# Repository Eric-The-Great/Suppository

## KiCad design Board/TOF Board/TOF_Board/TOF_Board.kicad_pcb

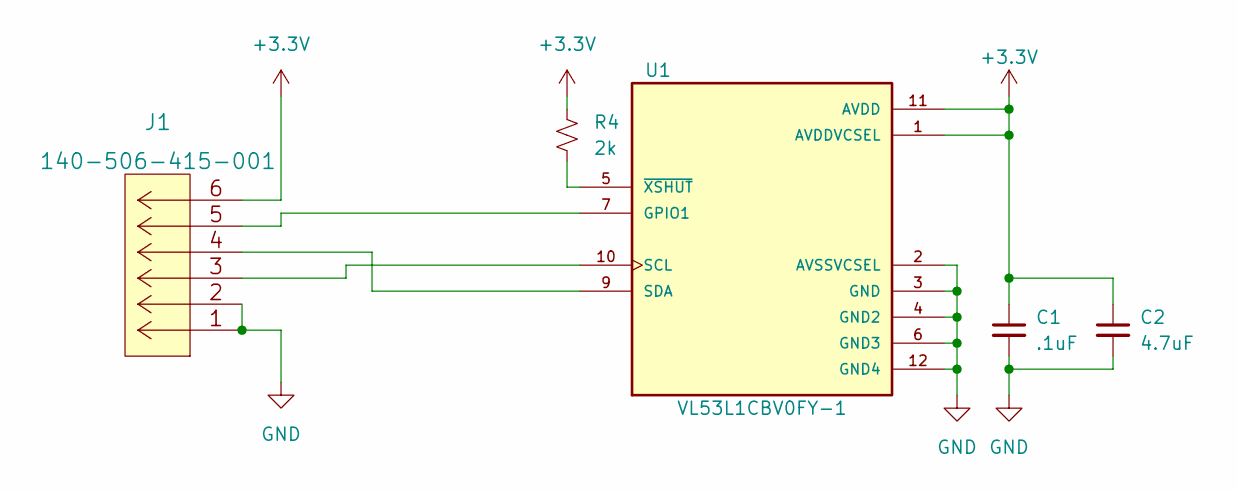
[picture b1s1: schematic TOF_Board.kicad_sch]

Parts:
C1: .1uF; R_0805_2012Metric
C2: 4.7uF; R_0805_2012Metric
J1: 140-506-415-001
R4: 2k; R_0805_2012Metric
U1: VL53L1CBV0FY-1; XDCR_VL53L1CBV0FY-1; PARTREV 3

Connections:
+3V3: C1.1, C2.1, J1.6, R4.1, U1.1 (AVDDVCSEL), U1.11 (AVDD)
GND: C1.2, C2.2, J1.1, J1.2, U1.2 (AVSSVCSEL), U1.3 (GND), U1.4 (GND2), U1.6 (GND3), U1.12 (GND4)
unnamed: J1.5, U1.7 (GPIO1)
unnamed: R4.2, U1.5 (~XSHUT)
unnamed: J1.4, U1.9 (SDA)
unnamed: J1.3, U1.10 (SCL)

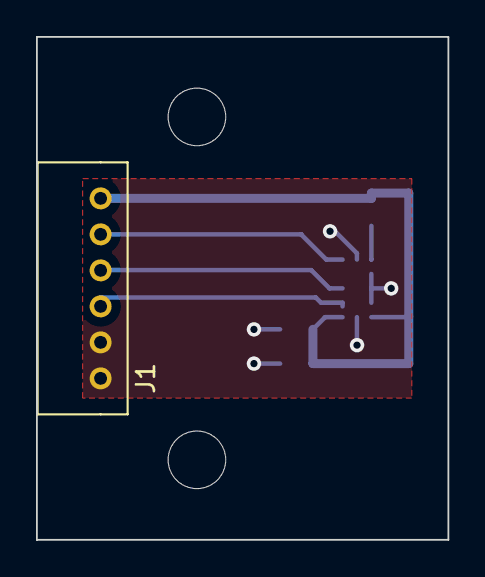
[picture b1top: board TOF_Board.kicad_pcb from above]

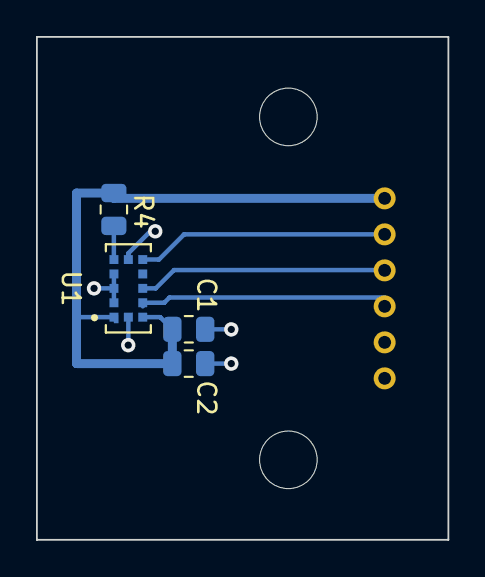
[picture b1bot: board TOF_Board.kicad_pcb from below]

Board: 2 copper layers, 22.9 x 27.9 mm, 5 parts (4 on the bottom side), 6 nets.

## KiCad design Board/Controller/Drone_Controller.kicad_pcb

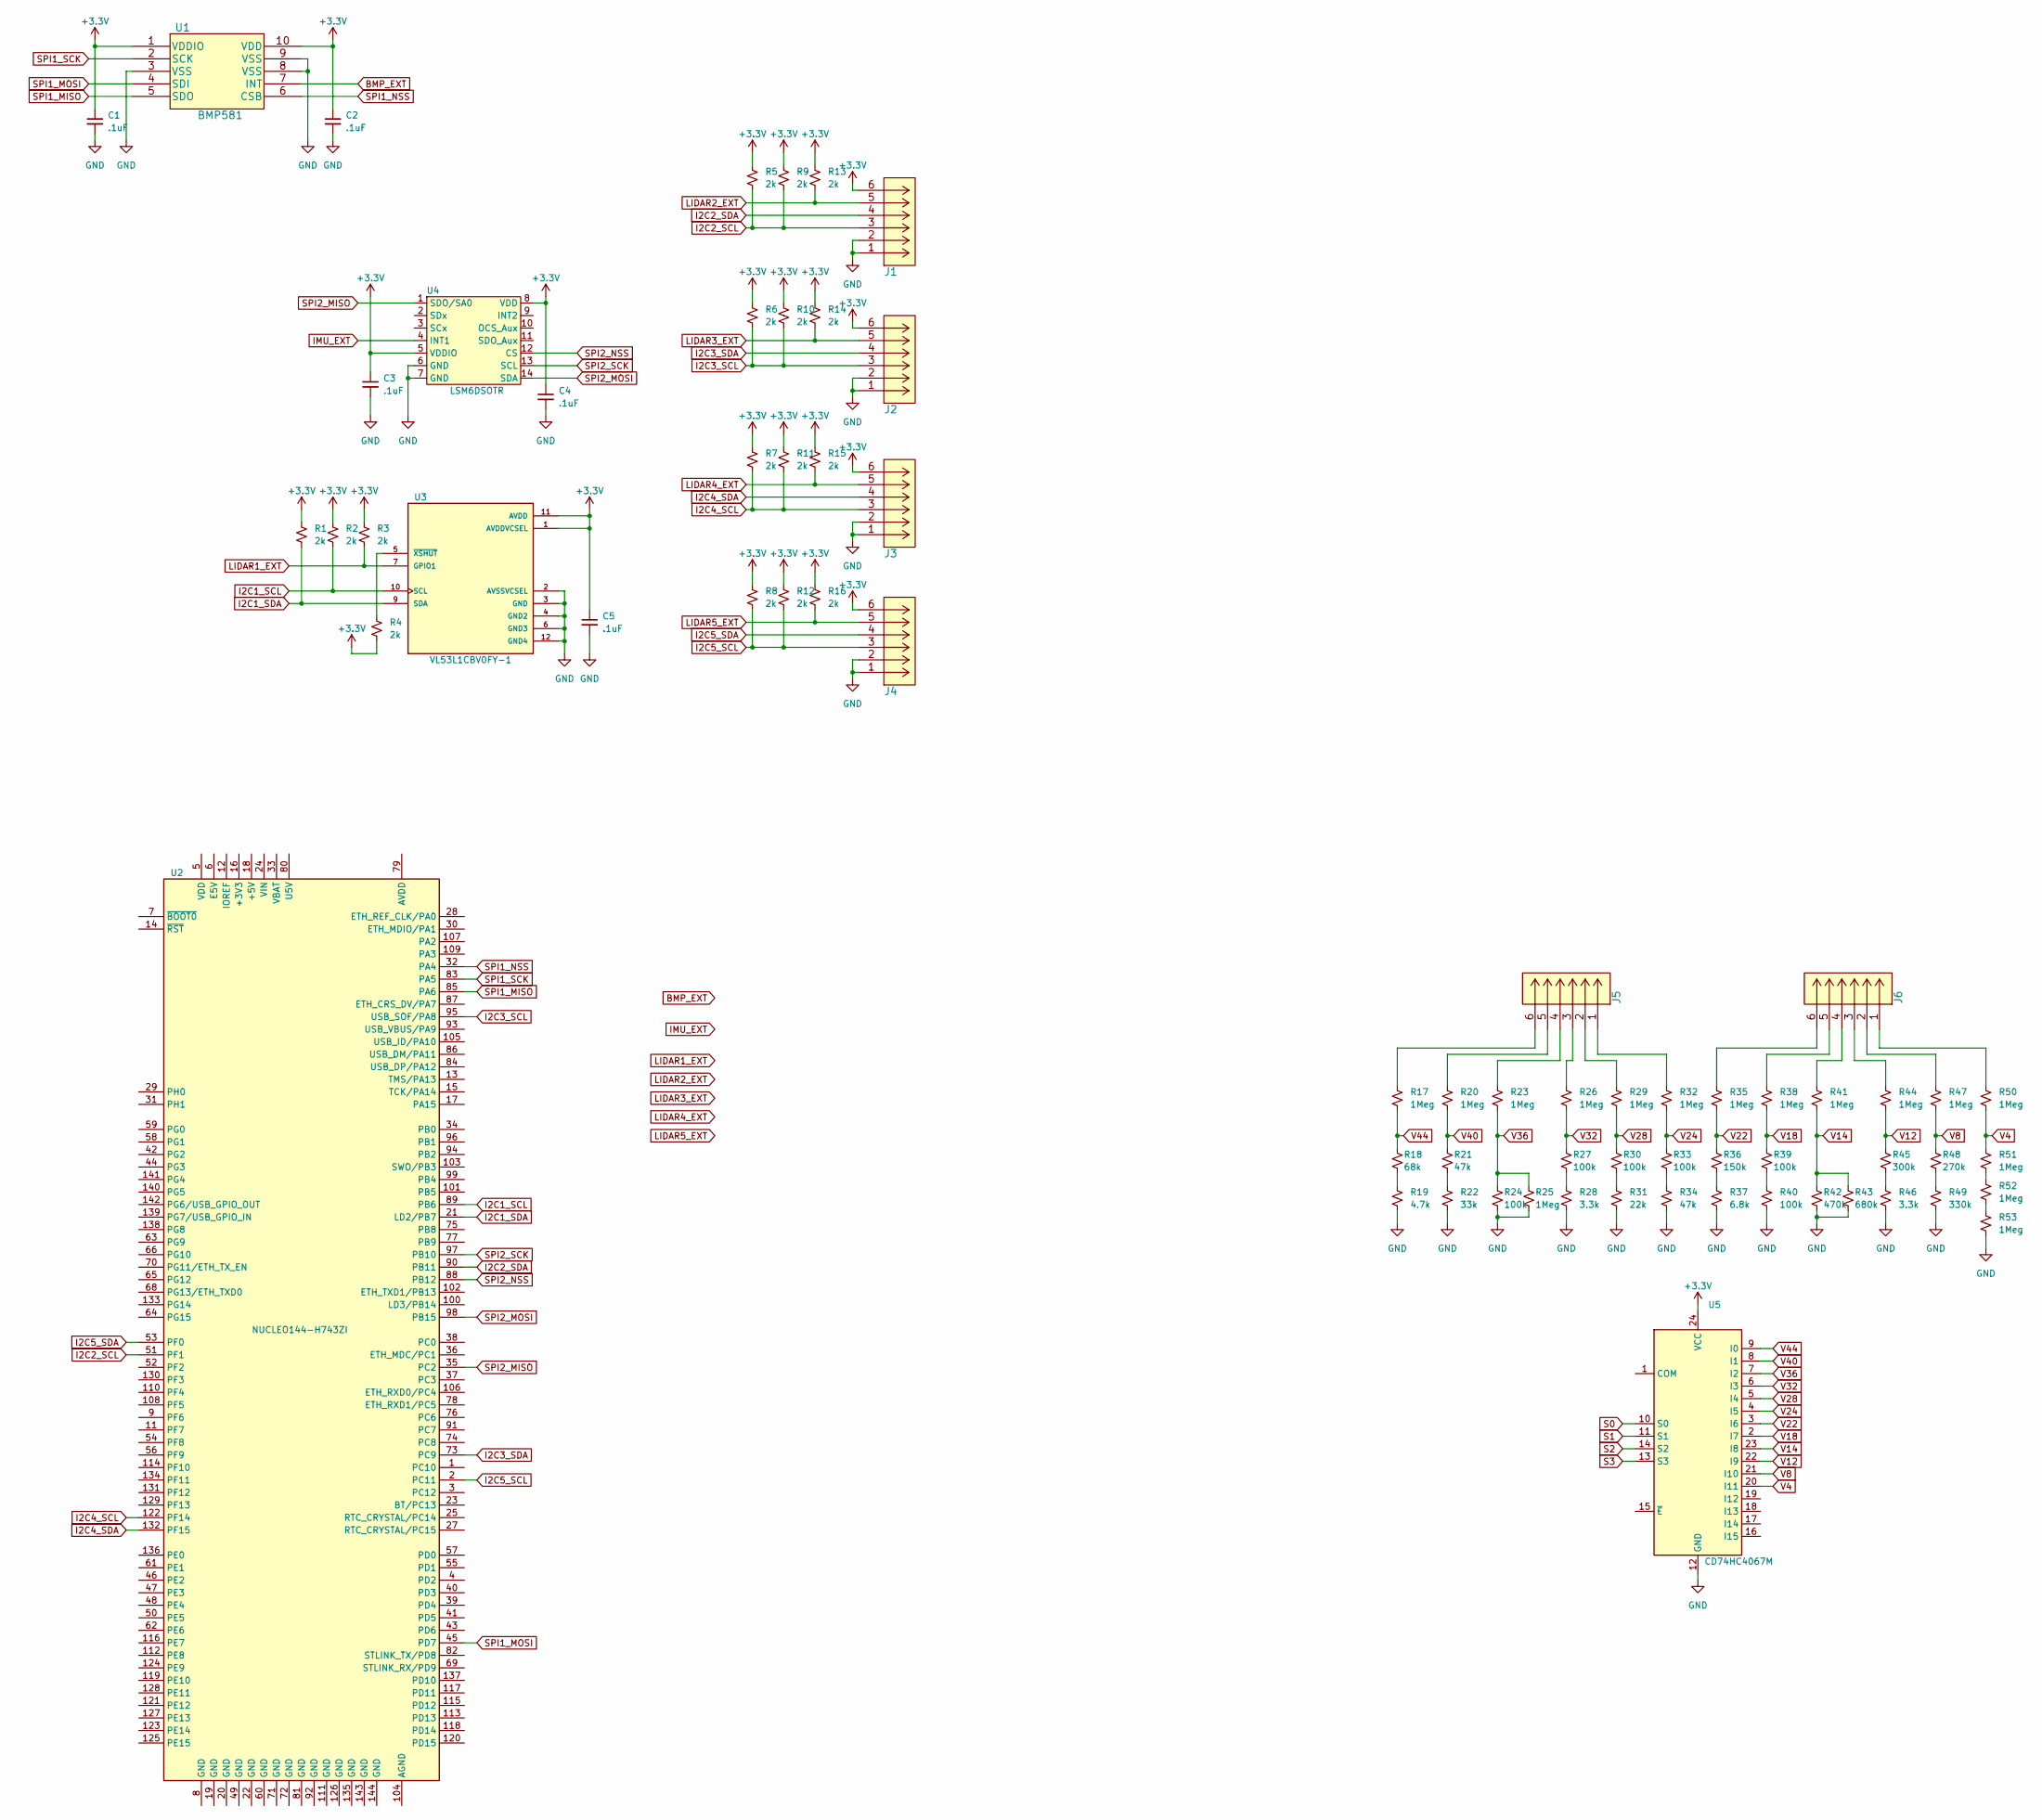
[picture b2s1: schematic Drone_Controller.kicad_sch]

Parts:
C1, C2, C3, C4, C5: .1uF; R_0805_2012Metric
J1, J2, J3, J4, J5, J6: 140-506-415-000
R1, R2, R3, R4, R5, R6, R7, R8, R9, R10, R11, R12, R13, R14, R15, R16: 2k; R_0805_2012Metric
R17, R20, R23, R25, R26, R29, R32, R35, R38, R41, R44, R47, R50, R51, R52, R53: 1Meg; R_0805_2012Metric
R18: 68k; R_0805_2012Metric
R19: 4.7k; R_0805_2012Metric
R21, R34: 47k; R_0805_2012Metric
R22: 33k; R_0805_2012Metric
R24, R27, R30, R33, R39, R40: 100k; R_0805_2012Metric
R28, R46: 3.3k; R_0805_2012Metric
R31: 22k; R_0805_2012Metric
R36: 150k; R_0805_2012Metric
R37: 6.8k; R_0805_2012Metric
R42: 470k; R_0805_2012Metric
R43: 680k; R_0805_2012Metric
R45: 300k; R_0805_2012Metric
R48: 270k; R_0805_2012Metric
R49: 330k; R_0805_2012Metric
U1: BMP581
U2: NUCLEO144-H743ZI; ST_Morpho_Connector_144_STLink
U3: VL53L1CBV0FY-1; XDCR_VL53L1CBV0FY-1; PARTREV 3
U4: LSM6DSOTR
U5: CD74HC4067M; SOIC-24W_7.5x15.4mm_P1.27mm

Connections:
+3V3: C1.1, C2.1, C3.1, C4.1, C5.1, J1.6, J2.6, J3.6, J4.6, R1.1, R2.1, R3.1, R4.2, R5.1, R6.1, R7.1, R8.1, R9.1, R10.1, R11.1, R12.1, R13.1, R14.1, R15.1, R16.1, U1.1 (VDDIO), U1.10 (VDD), U3.1 (AVDDVCSEL), U3.11 (AVDD), U4.5 (VDDIO), U4.8 (VDD), U5.24 (VCC)
BMP_EXT: U1.7 (INT)
GND: C1.2, C2.2, C3.2, C4.2, C5.2, J1.1, J1.2, J2.1, J2.2, J3.1, J3.2, J4.1, J4.2, R19.2, R22.2, R24.2, R25.2, R28.2, R31.2, R34.2, R37.2, R40.2, R42.2, R43.2, R46.2, R49.2, R53.2, U1.3 (VSS), U1.8 (VSS), U1.9 (VSS), U3.2 (AVSSVCSEL), U3.3 (GND), U3.4 (GND2), U3.6 (GND3), U3.12 (GND4), U4.6 (GND), U4.7 (GND), U5.12 (GND)
I2C1_SCL: R2.2, U2.89 (PB6), U3.10 (SCL)
I2C1_SDA: R1.2, U2.21 (LD2/PB7), U3.9 (SDA)
I2C2_SCL: J1.3, R5.2, R9.2, U2.51 (PF1)
I2C2_SDA: J1.4, U2.90 (PB11)
I2C3_SCL: J2.3, R6.2, R10.2, U2.95 (USB_SOF/PA8)
I2C3_SDA: J2.4, U2.73 (PC9)
I2C4_SCL: J3.3, R7.2, R11.2, U2.122 (PF14)
I2C4_SDA: J3.4, U2.132 (PF15)
I2C5_SCL: J4.3, R8.2, R12.2, U2.2 (PC11)
I2C5_SDA: J4.4, U2.53 (PF0)
IMU_EXT: U4.4 (INT1)
LIDAR1_EXT: R3.2, U3.7 (GPIO1)
LIDAR2_EXT: J1.5, R13.2
LIDAR3_EXT: J2.5, R14.2
LIDAR4_EXT: J3.5, R15.2
LIDAR5_EXT: J4.5, R16.2
unnamed: J5.1, R32.1
unnamed: J5.2, R29.1
unnamed: J5.3, R26.1
unnamed: J5.4, R23.1
unnamed: J5.5, R20.1
unnamed: J5.6, R17.1
unnamed: J6.1, R50.1
unnamed: J6.2, R47.1
unnamed: J6.3, R44.1
unnamed: J6.4, R41.1
unnamed: J6.5, R38.1
unnamed: J6.6, R35.1
unnamed: R4.1, U3.5 (~XSHUT)
unnamed: R18.2, R19.1
unnamed: R21.2, R22.1
unnamed: R27.2, R28.1
unnamed: R30.2, R31.1
unnamed: R33.2, R34.1
unnamed: R36.2, R37.1
unnamed: R39.2, R40.1
unnamed: R45.2, R46.1
unnamed: R48.2, R49.1
unnamed: R51.2, R52.1
unnamed: R52.2, R53.1
S0: U5.10 (S0)
S1: U5.11 (S1)
S2: U5.14 (S2)
S3: U5.13 (S3)
SPI1_MISO: U1.5 (SDO), U2.85 (PA6)
SPI1_MOSI: U1.4 (SDI), U2.45 (PD7)
SPI1_NSS: U1.6 (CSB), U2.32 (PA4)
SPI1_SCK: U1.2 (SCK), U2.83 (PA5)
SPI2_MISO: U2.35 (PC2), U4.1 (SDO/SA0)
SPI2_MOSI: U2.98 (PB15), U4.14 (SDA)
SPI2_NSS: U2.88 (PB12), U4.12 (CS)
SPI2_SCK: U2.97 (PB10), U4.13 (SCL)
V4: R50.2, R51.1, U5.20 (I11)
V8: R47.2, R48.1, U5.21 (I10)
V12: R44.2, R45.1, U5.22 (I9)
V14: R41.2, R42.1, R43.1, U5.23 (I8)
V18: R38.2, R39.1, U5.2 (I7)
V22: R35.2, R36.1, U5.3 (I6)
V24: R32.2, R33.1, U5.4 (I5)
V28: R29.2, R30.1, U5.5 (I4)
V32: R26.2, R27.1, U5.6 (I3)
V36: R23.2, R24.1, R25.1, U5.7 (I2)
V40: R20.2, R21.1, U5.8 (I1)
V44: R17.2, R18.1, U5.9 (I0)

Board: 4 copper layers, 69 parts (0 on the bottom side), 61 nets, no tracks yet.

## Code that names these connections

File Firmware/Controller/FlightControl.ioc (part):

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Mcu.Name=STM32H723ZGTx
Mcu.Package=LQFP144
Mcu.UserName=STM32H723ZGTx
PA1.GPIOParameters=GPIO_Label
PA1.GPIO_Label=RMII_REF_CLK
PA1.Mode=RMII
PA1.Signal=ETH_REF_CLK
PA10.GPIOParameters=GPIO_Label
PA10.GPIO_Label=USB_FS_ID
PA10.Mode=OTG/Dual-Role-Device-FS
PA10.Signal=USB_OTG_HS_ID
PA11.GPIOParameters=GPIO_Label
PA11.GPIO_Label=USB_FS_DM
PA11.Mode=OTG/Dual-Role-Device-FS
PA11.Signal=USB_OTG_HS_DM
PA12.GPIOParameters=GPIO_Label
PA12.GPIO_Label=USB_FS_DP
PA12.Mode=OTG/Dual-Role-Device-FS
PA12.Signal=USB_OTG_HS_DP
PA13(JTMS/SWDIO).GPIOParameters=GPIO_Label
PA13(JTMS/SWDIO).GPIO_Label=SWDIO
PA13(JTMS/SWDIO).Mode=Trace_Asynchronous_SW
PA13(JTMS/SWDIO).Signal=DEBUG_JTMS-SWDIO
PA14(JTCK/SWCLK).GPIOParameters=GPIO_Label
PA14(JTCK/SWCLK).GPIO_Label=SWCLK
PA14(JTCK/SWCLK).Mode=Trace_Asynchronous_SW
PA14(JTCK/SWCLK).Signal=DEBUG_JTCK-SWCLK
PA2.GPIOParameters=GPIO_Label
PA2.GPIO_Label=RMII_MDIO
PA2.Mode=RMII
PA2.Signal=ETH_MDIO
PA4.Mode=NSS_Signal_Hard_Output
PA4.Signal=SPI1_NSS
PA5.Mode=Full_Duplex_Master
PA5.Signal=SPI1_SCK
PA6.Mode=Full_Duplex_Master
PA6.Signal=SPI1_MISO
PA7.GPIOParameters=GPIO_Label
PA7.GPIO_Label=RMII_CRS_DV
PA7.Mode=RMII
PA7.Signal=ETH_CRS_DV
PA8.Mode=I2C
PA8.Signal=I2C3_SCL
PA9.GPIOParameters=GPIO_Label
PA9.GPIO_Label=USB_FS_VBUS
PA9.Mode=Activate_VBUS_FS
PA9.Signal=USB_OTG_HS_VBUS
PB0.GPIOParameters=GPIO_Label
PB0.GPIO_Label=LED_GREEN
PB0.Signal=GPIO_Output
PB10.Mode=Full_Duplex_Master
PB10.Signal=SPI2_SCK
PB11.Mode=I2C
PB11.Signal=I2C2_SDA
PB12.Mode=NSS_Signal_Hard_Output
PB12.Signal=SPI2_NSS
PB13.GPIOParameters=GPIO_Label
PB13.GPIO_Label=RMII_TXD1
PB13.Mode=RMII
PB13.Signal=ETH_TXD1
PB14.GPIOParameters=GPIO_Label
PB14.GPIO_Label=LED_RED
PB14.Signal=GPIO_Output
PB15.Mode=Full_Duplex_Master
PB15.Signal=SPI2_MOSI
PB3(JTDO/TRACESWO).GPIOParameters=GPIO_Label
PB3(JTDO/TRACESWO).GPIO_Label=SWO
PB3(JTDO/TRACESWO).Mode=Trace_Asynchronous_SW
PB3(JTDO/TRACESWO).Signal=DEBUG_JTDO-SWO
PB6.Mode=I2C
PB6.Signal=I2C1_SCL
PB7.Mode=I2C
PB7.Signal=I2C1_SDA
PC1.GPIOParameters=GPIO_Label
PC1.GPIO_Label=RMII_MDC
PC1.Mode=RMII
PC1.Signal=ETH_MDC
PC11.Mode=I2C
PC11.Signal=I2C5_SCL
PC13.GPIOParameters=GPIO_Label
PC13.GPIO_Label=B1 (Blue_User_Button)
PC13.Signal=GPIO_Input
PC14-OSC32_IN.Mode=LSE-External-Oscillator
PC14-OSC32_IN.Signal=RCC_OSC32_IN
PC15-OSC32_OUT.Mode=LSE-External-Oscillator
PC15-OSC32_OUT.Signal=RCC_OSC32_OUT
PC2_C.Mode=Full_Duplex_Master
PC2_C.Signal=SPI2_MISO
PC4.GPIOParameters=GPIO_Label
PC4.GPIO_Label=RMII_RXD0
PC4.Mode=RMII
PC4.Signal=ETH_RXD0
PC5.GPIOParameters=GPIO_Label
PC5.GPIO_Label=RMII_RXD1
PC5.Mode=RMII
PC5.Signal=ETH_RXD1
PC9.Mode=I2C
PC9.Signal=I2C3_SDA
PD10.Signal=GPIO_Output
PD7.Mode=Full_Duplex_Master
PD7.Signal=SPI1_MOSI
PD8.GPIOParameters=GPIO_Label
PD8.GPIO_Label=STLK_VCP_RX
PD8.Mode=Asynchronous
PD8.Signal=USART3_TX
PD9.GPIOParameters=GPIO_Label
PD9.GPIO_Label=STLK_VCP_TX
PD9.Mode=Asynchronous
PD9.Signal=USART3_RX
PE1.GPIOParameters=GPIO_Label
PE1.GPIO_Label=LED_YELLOW
PE1.Signal=GPIO_Output
PF0.Mode=I2C
PF0.Signal=I2C5_SDA
PF1.Mode=I2C
PF1.Signal=I2C2_SCL
PF14.Mode=I2C
PF14.Signal=I2C4_SCL
PF15.Mode=I2C
PF15.Signal=I2C4_SDA
PG11.GPIOParameters=GPIO_Label
PG11.GPIO_Label=RMII_TX_EN
PG11.Mode=RMII
PG11.Signal=ETH_TX_EN
PG13.GPIOParameters=GPIO_Label
PG13.GPIO_Label=RMII_TXD0
PG13.Mode=RMII
PG13.Signal=ETH_TXD0
PG7.GPIOParameters=GPIO_Label
PG7.GPIO_Label=USB_FS_OVCR
PG7.Signal=GPXTI7
PH0-OSC_IN.GPIOParameters=GPIO_Label
PH0-OSC_IN.GPIO_Label=MCO
PH0-OSC_IN.Mode=HSE-External-Clock-Source
PH0-OSC_IN.Signal=RCC_OSC_IN
PH1-OSC_OUT.Signal=RCC_OSC_OUT
RCC.HSE_VALUE=8000000
RCC.SYSCLKFreq_VALUE=550000000
RCC.SYSCLKSource=RCC_SYSCLKSOURCE_PLLCLK
board=NUCLEO-H723ZG
boardIOC=true

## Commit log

2022-08-06 I changed everything good luck idiot
2022-08-06 I have to update the suppository
2022-08-06 Yo yo yo
2022-08-06 we did stuff
2022-08-07 Testing
2022-08-07 Oops
2022-08-07 TOF board push
2022-08-07 added connector
2022-08-07 updated board with library parts
2022-08-07 updated TOF board
2022-08-08 added top load connector
2022-08-08 added battery mux and LIDAR connectors
2022-08-08 TOF board done (for now)
2022-08-08 changed firmware
